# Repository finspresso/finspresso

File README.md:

# finspresso

This repository contains the scripts used on the website [finspresso.com](https://www.finspresso.com/). The goal of [finspresso.com](https://www.finspresso.com/) is to write blog entry in the world of financials. Currently, there are the following main folders:

- [portfolio_tracker](https://github.com/finspresso/finspresso/tree/master/portfolio_tracker)
- [tax](https://github.com/finspresso/finspresso/tree/master/tax)
- [quant](https://github.com/finspresso/finspresso/tree/master/quant)
- [inflation](https://github.com/finspresso/finspresso/tree/master/inflation)
- [supermarket_tracker](https://github.com/finspresso/finspresso/tree/master/supermarket_tracker)

## Base package installation

For correct usage one needs the base package `portfolio_math`. To install it, execute:

```sh
python setup.py install
```

Have fun.

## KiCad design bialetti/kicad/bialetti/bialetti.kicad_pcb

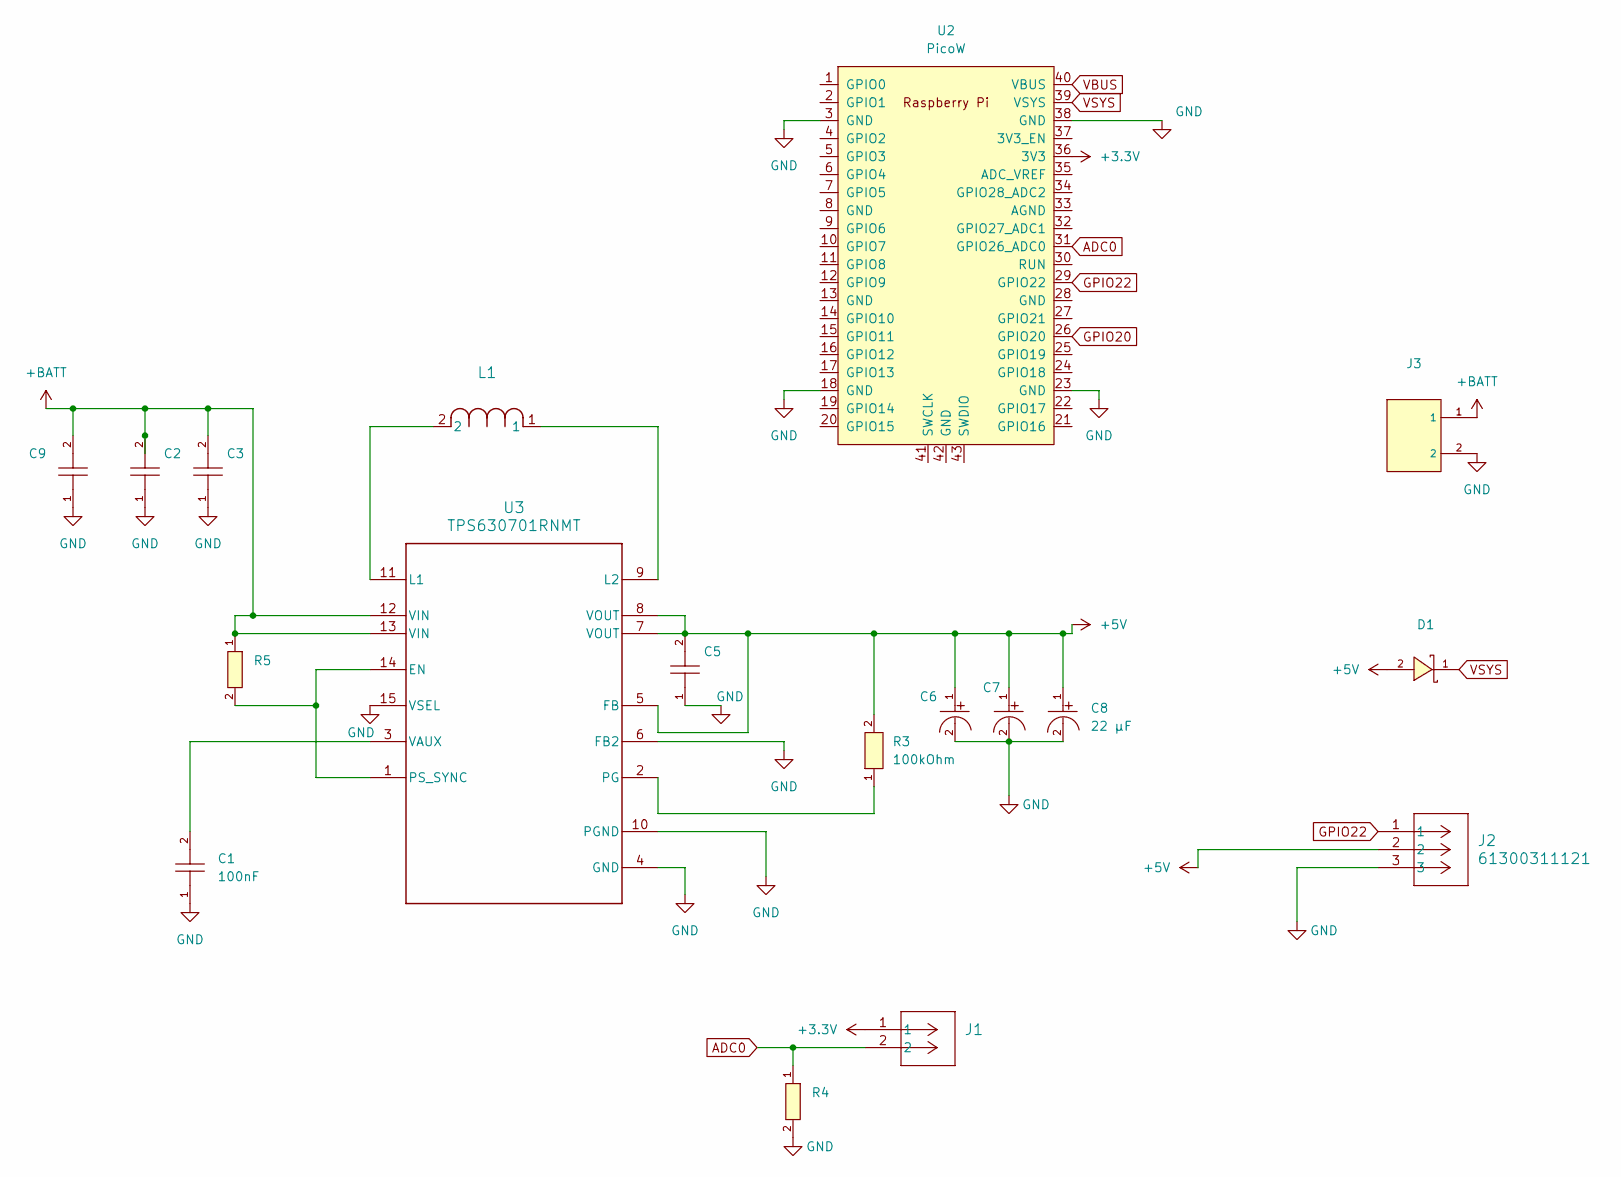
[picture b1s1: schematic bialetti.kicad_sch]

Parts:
C1: 100nF; C0201; LCSC C2894307
C2, C3, C5: 10 µF; C0402; LCSC C386033
C6, C7, C8: 22 µF; CAP-SMD_BD5.0-L5.3-W5.3-FD; LCSC C131119
C9: 10 µF; C0402; JLC 0402
D1: SS34F; SMAF_L3.5-W2.6-LS4.7-RD; LCSC C181208
J1: 61300211121; CONN_61300211121_WRE
J2: 61300311121; CONN03_6130_7P62X2P54_WRE
J3: B2B-PH-K-S(LF)(SN); CONN-TH_B2B-PH-K-S; LCSC C131337
L1: 1.5uH; IND-SMD_L4.0-W4.0; JLC SMD_L4.0-W4.0
R3: 100kOhm; R1206; LCSC C2991745
R4, R5: 10kOhm; R0805; LCSC C115295
U2: PicoW; RPi_Pico_SMD_TH
U3: TPS630701RNMT; RNM0015A; JLC VQFN-15(2.5x3)

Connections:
+3.3V: J1.1, U2.36 (3V3)
+5V: C5.2, C6.1, C7.1, C8.1, D1.2 (A), J2.2, R3.2, U3.5 (FB), U3.7 (VOUT), U3.8 (VOUT)
+BATT: C2.2, C3.2, C9.2, J3.1, R5.1, U3.12 (VIN), U3.13 (VIN)
ADC0: J1.2, R4.1, U2.31 (GPIO26_ADC0)
GND: C1.1, C2.1, C3.1, C5.1, C6.2, C7.2, C8.2, C9.1, J2.3, J3.2, R4.2, U2.3 (GND), U2.18 (GND), U2.23 (GND), U2.38 (GND), U3.4 (GND), U3.6 (FB2), U3.10 (PGND), U3.15 (VSEL)
GPIO20: U2.26 (GPIO20)
GPIO22: J2.1, U2.29 (GPIO22)
unnamed: R5.2, U3.1 (PS_SYNC), U3.14 (EN)
unnamed: L1.2, U3.11 (L1)
unnamed: L1.1, U3.9 (L2)
unnamed: R3.1, U3.2 (PG)
unnamed: C1.2, U3.3 (VAUX)
VBUS: U2.40 (VBUS)
VSYS: D1.1 (K), U2.39 (VSYS)

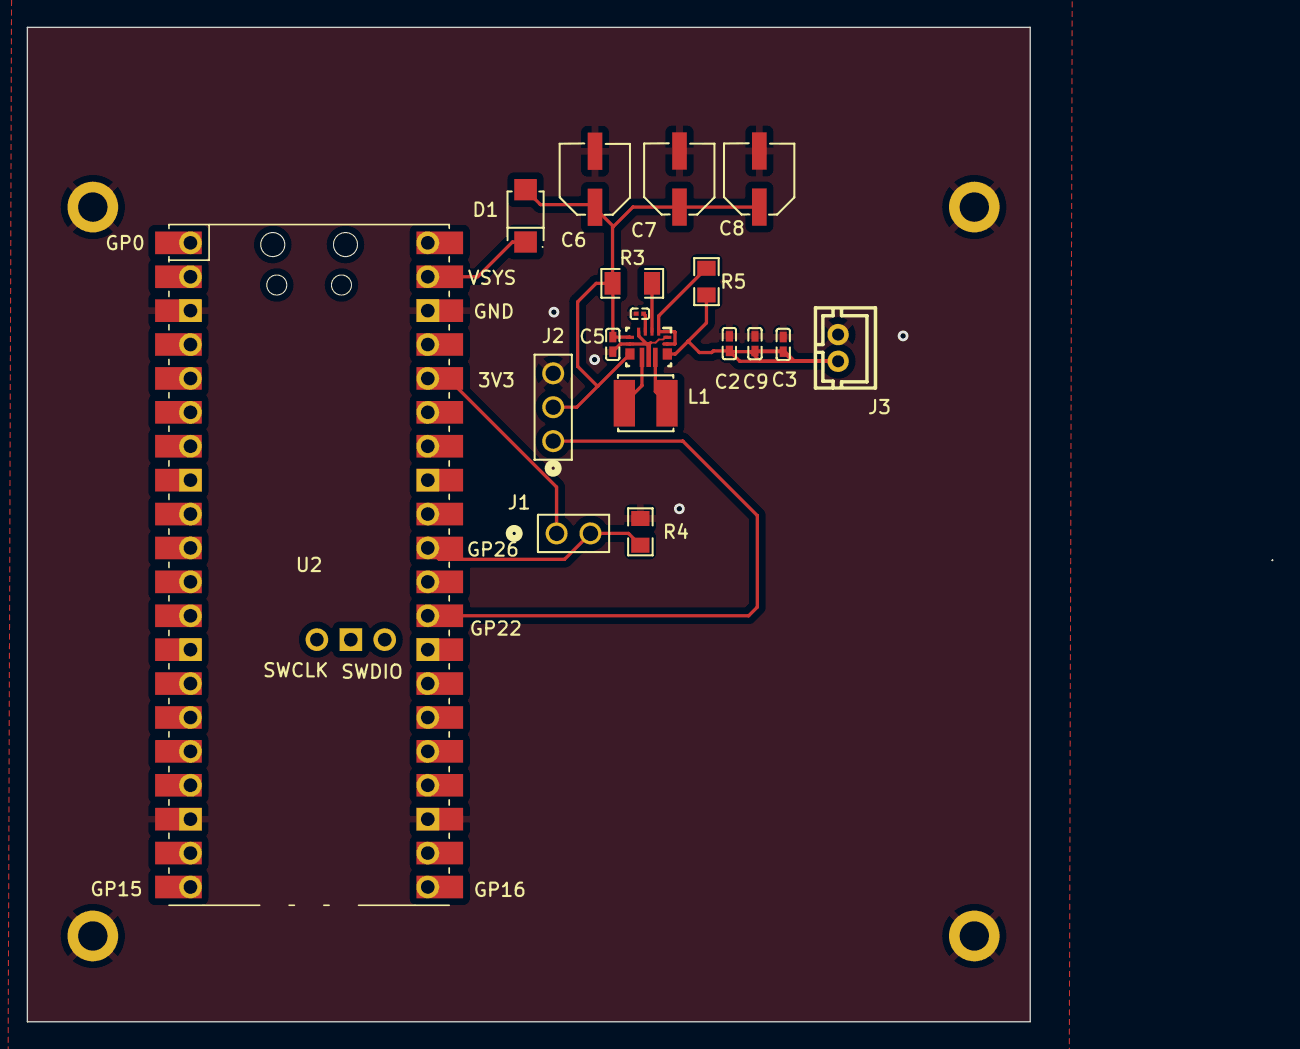
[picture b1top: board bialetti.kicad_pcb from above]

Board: 2 copper layers, 93.3 x 74.5 mm, 18 parts (0 on the bottom side), 12 nets.

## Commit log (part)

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2023-03-18 Add subcategories to translation files
2023-03-26 Translate also subcategories
2023-03-26 Improving translations
2023-03-26 Upload subcategories to SQL db
2023-03-27 Add second Graph
2023-03-27 Make it work decoupled
2023-03-28 Load subcategories
2023-03-28 Retrieve sucategory data from database
2023-03-28 Update subcategories
2023-03-29 Use same colors for subcategories
2023-03-29 Remove debuggin lines
2023-03-29 Small improvements
2023-03-29 Capitalize only first letter
2023-03-29 Proper labelling
2023-03-29 Make it work for wordpress renderer
2023-03-30 Add legend for evolution plots
2023-03-30 Update translation files
2023-03-30 Fix case of going back to Total
2023-04-15 Also extract other category
2023-04-16 Add compare tool
2023-04-22 Add two selectable categories
2023-04-23 Add relative checkbox
2023-04-23 Use also drilldown dataframe
2023-04-23 Use first valid index for relative
2023-04-23 Add translatation to compare tab
2023-04-23 Add vegetables to frozen translation
2023-04-23 Sort the subcategories
2023-04-23 Update portfolio_tracker to 2023
2023-05-01 Show legend in KVPI plot
2023-05-01 Make upload function global
2023-05-01 Upload also merged LIK/KVPI df
2023-05-01 Replace table instead of appending
2023-05-01 Start with comapre_evolution.html
2023-05-01 Select correct table
2023-05-01 Sort categories
2023-05-01 Visualize two categories
2023-05-07 Add zoom option in compare graph
2023-05-07 Add pan option
2023-05-07 Add reset view button
2023-05-07 Reset view after graph is updated
2023-05-08 Add enable/disable checkbox
2023-05-08 Enable/Disable graph based on checkbox
2023-05-08 Do not input categories into update function
2023-05-08 Correctl init rescale to null
2023-05-08 Call updateCheckboxes in updateGraph
2023-05-08 Make max_graph global
2023-05-08 Allow up to 5 categories
2023-05-08 Make points smaller
2023-05-09 Show relative growth per category in legend
2023-05-09 Show KVPI categories in gray background
2023-05-09 Update translation
2023-05-09 Fix bug in compare tool with sorting
2023-05-10 Adding supermarket_tracker
2023-05-10 Add launch.json file
2023-05-11 Use Selenium to get prices
2023-05-11 Add option to store screenshots
2023-05-11 Add option to collect all products
2023-05-11 Get all prices from the overview page
2023-05-11 Except Timeout
2023-05-12 Store prices to .xslx file
2023-05-14 Store thumbnails of products
2023-05-18 Add reference folder
2023-05-18 Create reference product json
2023-05-18 Print out new and discontinued articles
2023-05-18 Add Express option + timetracking
2023-05-18 Add introduction and disconutation date
2023-05-18 Add option update reference.json offline
2023-05-18 Add option to update reference .json file
2023-05-18 Only consider active articles
2023-05-18 Categorize new articles
2023-05-18 Update CHDVD distributions
2023-05-18 Leave non-ascii characters in .json
2023-05-19 Add db_interface_package
2023-05-20 Add creation of metadata table
2023-05-20 Create/update prices table
2023-05-20 Dynamically alter table with new columns
2023-05-21 Add README.md for supermarket_tracker
2023-05-21 Create prices tables with auto-increment column
2023-05-21 Do not upload dataframe index
2023-05-21 Adding update at column
2023-05-27 Add browser folder
2023-05-27 Remove old folder
2023-05-27 Residual changes
2023-05-27 Ading lik_json files for category
2023-05-27 Add .gitignores
2023-05-27 Add correct folder structure for soft link to README
2023-05-27 Add Chrome
2023-05-27 Use correct folder names
2023-05-27 Improve explanation
2023-05-28 Add notes to README for supermarket
2023-05-28 Use env variable PROJECT_FOLDER
2023-05-28 Remove empty space
2023-05-28 Use correct hyperlink
2023-05-28 Use correct html file path
2023-05-28 Use mbudget_tracker as an example
2023-05-28 Add php_files for supermarket_tracker
2023-05-28 Download articles from MYSQL db
2023-05-28 Show product URL
2023-05-28 Describing in README download of products
2023-05-28 Add .php file to get price data
2023-05-28 Adding .gitignore
2023-05-28 Fix README
2023-05-29 Adding product_reference.json section in README
2023-05-29 Add section of updating reference.json
2023-05-29 Remove image
2023-05-29 Adding section of updating metadata table
2023-05-29 Add bash script to process all-in-one
2023-05-29 Adding forgotten images
2023-05-29 Adding interactive mode
2023-05-29 Adding averages
2023-05-29 Add include to metadata
2023-05-29 Log line
2023-06-03 Add Makefile
2023-06-03 Add dropdown for averages
2023-06-03 Add Chart to visualize different prices
2023-06-03 Use MBudget color code
2023-06-04 Use Arial as font
2023-06-04 Only show products that are labelled include
2023-06-04 Extract the non_unique names
2023-06-10 Extract more info per article for name
2023-06-10 Use regex mask to determine category
2023-06-10 Check for duplicate during creations
2023-06-10 Update new reference.json and .xlsx file
2023-06-10 Updated mbudget_prices.xlsx
2023-06-10 Add .gitignore
2023-06-10 Change to portfolio_tracker.py
2023-06-11 Style MBudget file properly
2023-06-23 Update all the prices
2023-06-23 Do not use double ampersand due to wordpress
2023-06-23 Use only numeric values for mean
2023-06-24 Force black as font color in mbudget_tracker.html
2023-06-24 Add search fields for select boxes
2023-06-24 Init Average checkbox as unchecked
2023-06-25 Add selection box for other category
2023-06-25 Remove debug statements
2023-06-25 Disable if unchecked
2023-07-02 Update inflation data
2023-07-02 Download LIK data via Python command
2023-07-08 Add checker for update before downloading
2023-07-09 Update latest data to dUpdate latest data to db
2023-07-09 Fix correct category
2023-07-09 Fix category
2023-07-16 Updating product_reference for mbudget
2023-07-16 Add commit and push in update_all.sh
2023-07-23 Add mbduget update script
2023-08-20 Remove not necessary libraries
2023-08-27 Revert "Remove not necessary libraries"
    This reverts commit 02a2d2262d8b6169289f293496067fb0ccfd33ac.
2023-08-27 Typo
2023-08-30 Add dial interface
2023-08-31 Adding support plate
2023-09-01 Add temperature logging script
2023-09-01 Add LED display
2023-09-02 Add adaptive log file name
2023-09-02 Add docker-compose.yml for MySQL and phpmyadmin
2023-09-02 Add volume to make data persistent
2023-09-03 Add Dockerfile for Apache server
2023-09-03 Add php-apache docker image
2023-09-05 Add update_lik.sh
2023-09-05 Small fix for mbudget script
2023-09-05 Make it look nice on mobile
2023-09-05 Small fix
2023-09-05 Tuning
2023-09-05 Tuning range
2023-09-05 Make it nicely adaptive
2023-09-06 Reduce empty space lik_evolution.html
2023-09-06 Add option to download data from SQL table
2023-09-06 Check for new data before uploading
2023-09-07 Use Debian version for MYSQL container
2023-09-07 Install mysqli in apache-php image
2023-09-07 Use dedicated volume
2023-09-07 Force to not cache ajax call
2023-09-07 Use prodcut_reference.json from master
2023-09-07 Rename to Dockerfile_Apache_PHP
2023-09-07 Simpler transfer
2023-09-07 rename to Apache_PHP.Dockerfile
2023-09-07 Add specific MySQL file as finspresso.com
2023-09-07 Add correct db name
2023-09-07 Add axes labels
2023-09-08 Add Docker container for supermarket_tracker
2023-09-10 Adding supermarket_tracker to docker-compose
2023-09-10 Different signature
2023-09-10 Make supermarket_tracker work for mbudget
2023-09-10 Clone repo to install db_interface lib
2023-09-10 Small bug
2023-09-10 Revert "Small bug"
    This reverts commit f094e75ecc6e517edd1e95bdde0adf03dca0eafc.
2023-09-10 Add non-interactive mode
2023-09-10 Enable db upload from container
2023-09-10 Fix extension button search
2023-09-16 Update interface
2023-09-17 Work with cloned repo
2023-09-17 Install gh cli
2023-09-17 test.tt
2023-09-17 Set git credentials
2023-09-19 Improvements
2023-09-24 Add chamfer
2023-09-24 Add proper chamfer
2023-10-01 Add creation of branch
2023-10-01 Add auto-PR creation
2023-10-01 Add pre-commit installation in dockerfile
2023-10-02 Add pre-commit
2023-10-02 next
2023-10-07 Add FreeCad format for stepper_support
2023-10-07 Add base branch
2023-10-07 Remove not needed git push
2023-10-08 Add docker volume for screenshots
2023-10-08 Do not create data folder in Dockerfile
2023-10-08 do not source bash_aliases in container
2023-10-08 Create mbudget folder
2023-10-08 Adding file
2023-10-08 Add portwarding command
2023-10-09 NExt commit
2023-10-15 Improve support dimensions
2023-10-21 Shift rotation axis of dial
2023-10-22 Fix typo
2023-10-29 Add button press to start/stop process
2023-10-29 Create credentials docker-volume
2023-10-29 New next
2023-10-29 Add LED feedback
2023-11-05 Shift chamfer
2023-11-05 Add tornado webserver
2023-11-05 Adding supermarket_index
2023-11-05 Call webui from entrypoint.sh
2023-11-11 Intermittent commit
2023-11-11 Shift support by 5mm
2023-11-11 Add new dividend
2023-11-11 Update dividend CHDVD
2023-11-11 Update VEUR
2023-11-11 Update VEUR and SIXT
2023-11-11 Pass .html file as parameter in entrpoint
2023-11-11 Add index_file to handler
2023-11-12 Execute MBudget tracker
2023-11-12 Input full execution file path
2023-11-12 Add new articles to dictionary
2023-11-18 Add stuff dockerfile
2023-11-18 Slightly shift it downward
2023-11-19 Do not copy reference over
2023-11-24 Also shift Chamferwq
2023-12-09 Add servo support
2023-12-09 Adaptions servo support
2023-12-09 Add servo_interface
2023-12-10 Move container to base folder
2023-12-10 Make it work form base folder
2023-12-10 Update requirements
2023-12-10 Build supermarket_tracker from base folder
2023-12-10 Use different folders
2023-12-10 Add index_container.html
2023-12-17 Work with holes
2023-12-23 Add servo actuation Arduino script
2023-12-23 Control it with pontetiometer
2024-01-02 Adding thermistor for RPI Pico
2024-01-14 Adding readout
2024-01-14 Only update if new articles there
2024-01-27 Add KiCAD files for PCBA
2024-01-28 Update drawings
2024-02-11 Start drawing for SunFounder servo horn
2024-02-11 Adding servo_support stuff
2024-03-10 Update servo support with smaller bore
2024-03-16 Update stepper interface
2024-03-24 Update servo_support
2024-03-24 Fixing issue with proceed button
2024-03-30 Update year
2024-04-01 Adding micropython coffee.py
2024-04-01 Fix coffee.py
2024-04-01 Update servo support
2024-04-01 Adding support only
2024-05-19 Adding hello_world.c
2024-05-19 Make it build it
2024-05-20 Add pontetiometer example
2024-05-20 Add coffee_control
2024-05-20 Output PWM levels based on pontetiometer input
2024-05-20 Use GPIO 22 as output pin
2024-06-09 Make coffee_control work
2024-06-09 Increase the angle to 270°
2024-06-09 Increase to 270°
2024-06-16 Add new servo support
2024-07-08 New freecad file
2024-07-28 Adding PCBA interface
2024-07-28 Add it M2 threaded holes
2024-07-28 Adding proper rework
2024-07-28 Add 4 holes
2024-07-28 Update xpath
2024-08-18 Redraw Servo Support
2024-08-18 Updating PCBA interface
2024-08-18 Update Servo interface
2024-08-25 Add LED_flashing in c code
2024-08-26 Add sixt dividend
2024-08-26 Update CHDVD dividend
2024-08-26 Use current year more adaptive
2024-08-26 Adding temp_measurement
2024-09-06 Update PCBA interface
2024-09-08 Add servo interface
2024-09-15 Formatting
2024-09-15 Update servo_interface
2024-09-29 Click on extension button
2024-10-06 Clean up
2024-11-09 Update to latest style of page
2024-12-15 Update servo_interface and servo support
2025-02-02 Update Makefile
2025-02-02 Use latest image tag
2025-02-02 Ensure start-maximized
2025-02-02 Tag image with commit
2025-02-02 Use folder with .xlsx file
2025-02-02 Fail gracefully
2025-03-29 Some fixes with new code
2025-03-30 Update dividends
2025-03-30 Go with no-headless
2025-03-30 Revert "Go with no-headless"
    This reverts commit e6ee855e83563b804373d6a864a8a75596665bcf.
2025-04-13 Different xpath
2025-04-13 Start virtual display
2025-04-13 go for non-headless
2025-04-18 Add specific webbrowser version
2025-04-27 Restart Xvfb
2025-04-27 Add verbose output
